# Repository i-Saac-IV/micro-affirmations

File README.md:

# µAffirmations
A microcontroller-based affection-giving MACHINE!

> [!IMPORTANT]
> This project is currently a work-in-progress, there __will__ be things that don't work, please bear with me will I work out the kinks!

# Table of Contents
- [Usage Guide](#usage-guide)
  - [Hardware](#hardware)
  - [Firmware](#firmware)
- [Photos](#photos)
- [Project Updates](#project-updates)
- [Copyright and Licensing](#copyright-and-licensing)
- [Contact](#contact)

# Usage Guide
## Hardware
The PCB files can be found [here](/hw/pcb/micro-affirmations.zip), be sure of order a solder stencil too(ideally with a stencil unless you love hand-soldering 200+ SMD connections). The [BOM](/hw/pcb/bom/ibom.html) will provide you with a list of parts required and their placements. Due to the limited size on the PCB, many of the reference designators have been removed to save space. Because of this, you will likely need to have KiCAD or the iBOM running as you are placing components. Or you can guess I suppose...

## Firmware
You will need access to an ST-Link programming device and have [stm32-for-vscode](https://open-vsx.org/extension/bmd/stm32-for-vscode) extension installed. Once you're ready, upload the code by:
- Cloning the repository
- Open in VS code
- Connect the ST-Link programmer to your computer
- Connect the µAffirmations' programming port to the ST-Link programmer
- Ensure the µAffirmations board is powered
- Open the STM32 for VS Code extention
- Click __Flash STM32__

### Message customisation
This device allows the user to create their own custom messages to be displayed on the LED matrix, to provide your messages, modify the following code found in [this](/Core/Src/messages.c) file.

For axample:
```c
__weak const char *messages[] = {
    "This is the first custom message!",
    "Below is a list of supported characters...",
    "!\"#$%&'()*+,-./0123456789:;<=>?@ABCDEFGHIJKLMNOPQRSTUVWXYZ[\\]^_`abcdefghijklmnopqrstuvwxyz{|}~"
};
```

# Photos
<table align="center">
  <tr>
    <td align="center">
      <br>
      <b>Programming port broken in RevB of the PCB</b>
    </td>
  </tr>
</table>

# Project Updates
## Hardware [RevD](https://github.com/i-Saac-IV/micro-affirmations/tree/v0.9.3)
After considerable development to the code, I found out that I had not connected the supercapacitor voltage sensing circuit to a ADC capable pin, this has been corrected. I also found that if the input voltage of the charging IC is greater than the output voltage = 100mV the bucking function of the IC is bypassed (meaning if the input is 5V the output is also 5V, bad for the STM chip), this has been fixed with the linear regulator.

## Hardware [RevC](https://github.com/i-Saac-IV/micro-affirmations/tree/v0.9.2)
After futher testing the following fixes to the hardware design have been made:
- The programming port has been connected to the correct pins on the mircocontroller
- The layout of the components has been adjusted for easier access to the push button
- The supercapacitor management circuit has been de-routed as per the spec sheet
- I added a QR to the PCB, because I could...

## Hardware [RevB](https://github.com/i-Saac-IV/micro-affirmations/tree/v0.9.1)
After hardware tesing the following fixes have been made to the hardware design:
- Supercapacitor charging circuit, now uses a dedecated IC
- LED matrix layout, the LED spacing has been decreased
- LED brightness was assessed and appropriate resistor have been selected
- The overall PCB dimentions have shrunk to 70x40mm
<table align="center">
  <tr>
    <td align="center">
      <br>
      <b>RevB PCB</b>
    </td>
  </tr>
</table>

## Hardware [RevA](https://github.com/i-Saac-IV/micro-affirmations/tree/v0.9.0)
Initial hardware design.

# Copyright and Licensing
See [licence](LICENSE) for in depth info.
<!--
This project uses the following third-party libraries:

- Lib ( License)

Copyright and license terms belong to their respective authors.

Contact me if anything here is incorrect.
-->

# Contact
If you'd like to get in touch, feel free to reach out!
<p>

</p>

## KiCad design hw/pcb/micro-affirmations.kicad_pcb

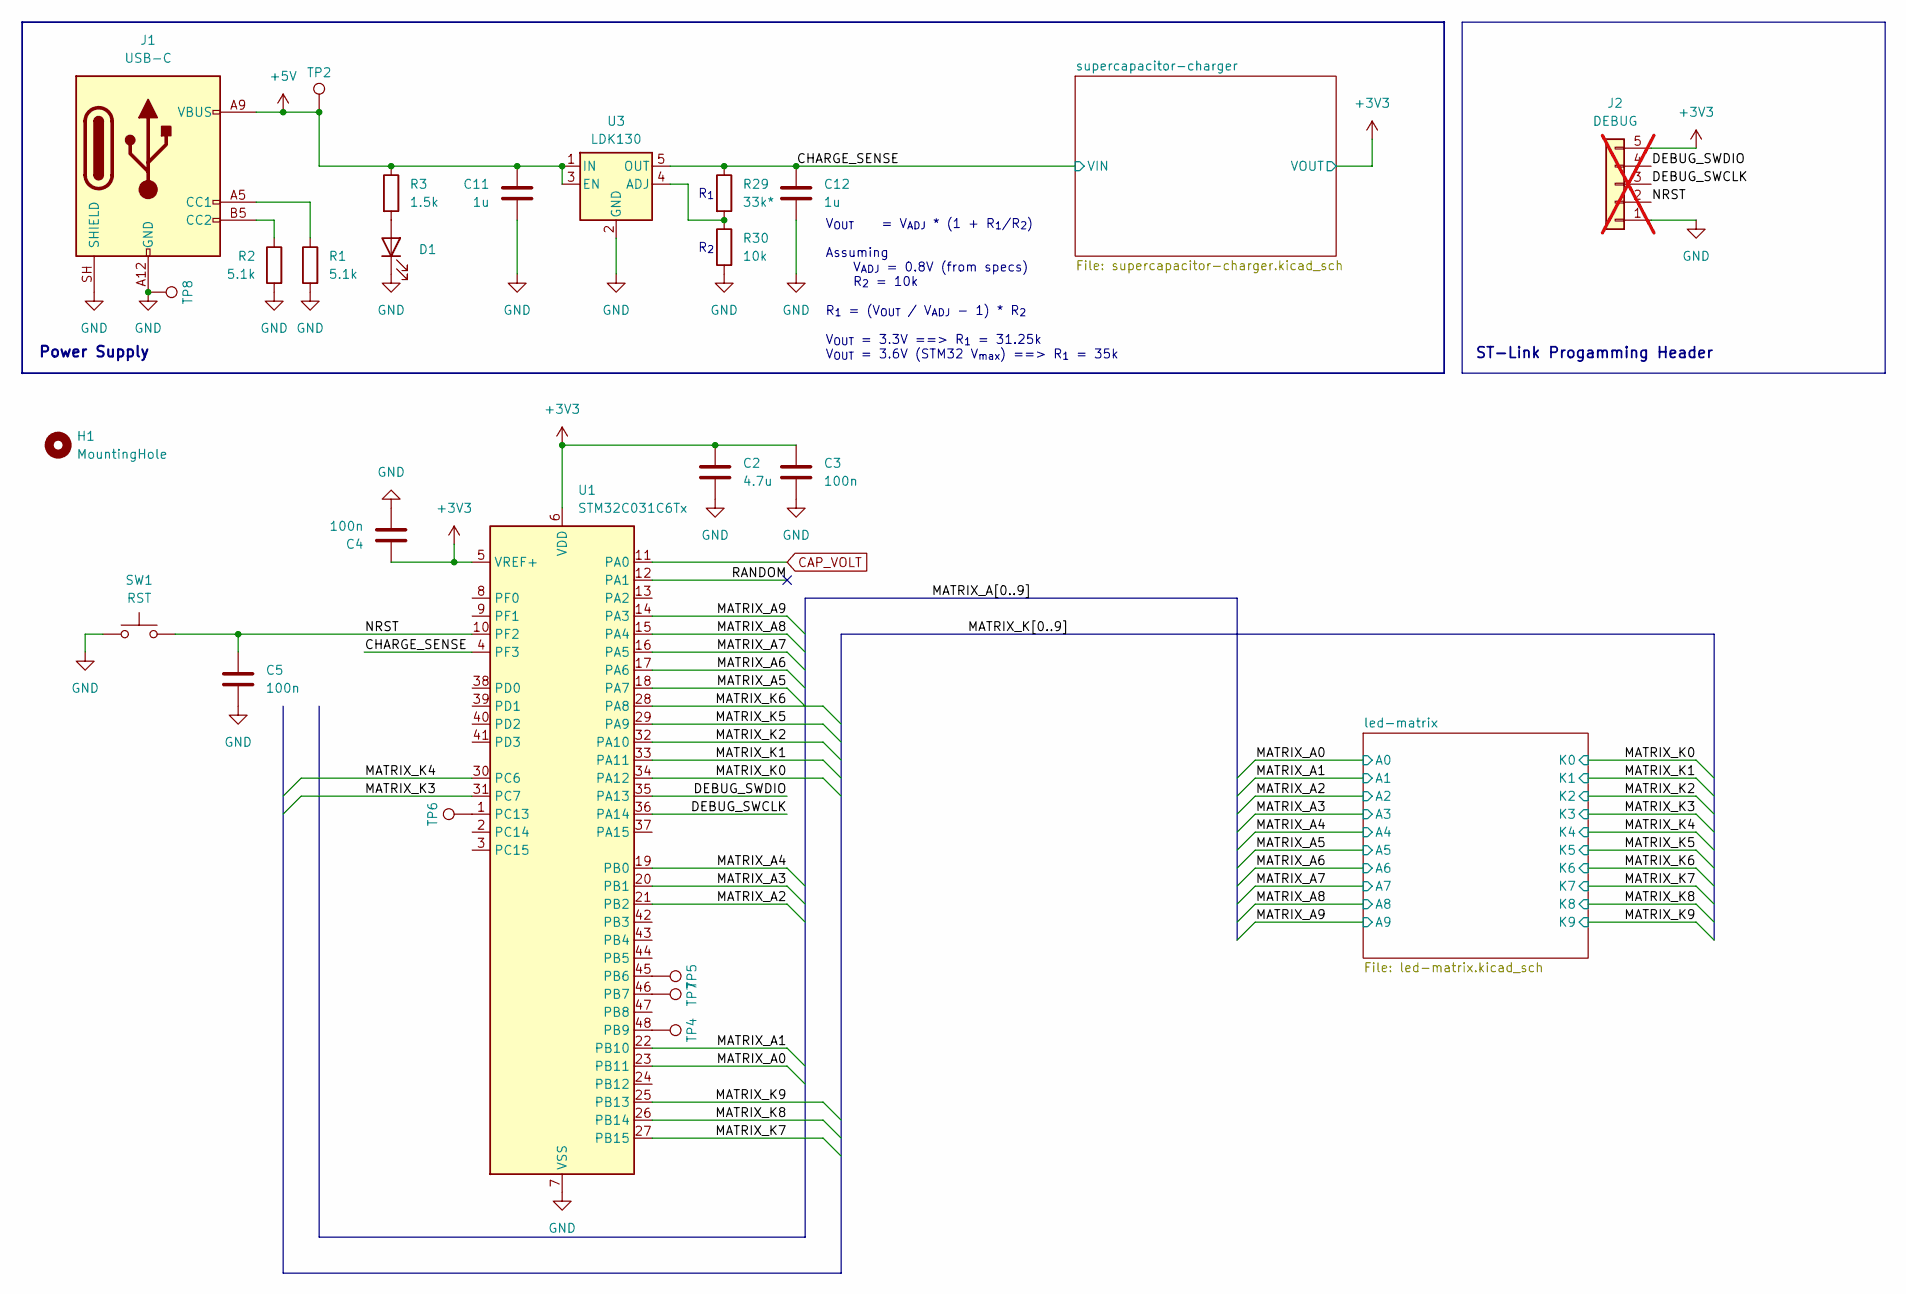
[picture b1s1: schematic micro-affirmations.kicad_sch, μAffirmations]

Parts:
C2: 4.7u; C_0805_2012Metric
C3, C4, C5: 100n; C_0805_2012Metric
C11, C12: 1u; C_0603_1608Metric
D1: CHARGE; D_0603_1608Metric
H1: MountingHole; MountingHole_2.2mm_M2
J1: USB-C; 2171750001_MOL
J2: DEBUG; PinHeader_1x05_P2.54mm_Vertical; not fitted
R1, R2: 5.1k; R_0603_1608Metric
R3: 1.5k; R_0603_1608Metric
R29: 33k*; R_0603_1608Metric
R30: 10k; R_0603_1608Metric
SW1: RST; TL1030_A
TP2, TP4, TP5, TP6, TP7, TP8: TestPoint; TestPoint_Pad_D1.0mm
U1: STM32C031C6Tx; LQFP-48_7x7mm_P0.5mm
U3: LDK130; SOT-23-5

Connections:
+3V3: C2.1, C3.1, C4.1, J2.5, U1.5 (VREF+), U1.6 (VDD); also elsewhere on the board
+5V: C11.1, J1.A9 (VBUS), J1.B9 (VBUS), R3.1, TP2.1 (1_1), U3.1 (IN), U3.3 (EN)
/CHARGE_SENSE: C12.1, R29.1, U1.4 (PF3), U3.5 (OUT); also elsewhere on the board
/DEBUG_SWCLK: J2.3, U1.36 (PA14)
/DEBUG_SWDIO: J2.4, U1.35 (PA13)
/MATRIX_A0: U1.23 (PB11); also elsewhere on the board
/MATRIX_A1: U1.22 (PB10); also elsewhere on the board
/MATRIX_A2: U1.21 (PB2); also elsewhere on the board
/MATRIX_A3: U1.20 (PB1); also elsewhere on the board
/MATRIX_A4: U1.19 (PB0); also elsewhere on the board
/MATRIX_A5: U1.18 (PA7); also elsewhere on the board
/MATRIX_A6: U1.17 (PA6); also elsewhere on the board
/MATRIX_A7: U1.16 (PA5); also elsewhere on the board
/MATRIX_A8: U1.15 (PA4); also elsewhere on the board
/MATRIX_A9: U1.14 (PA3); also elsewhere on the board
/MATRIX_K0: U1.34 (PA12); also elsewhere on the board
/MATRIX_K1: U1.33 (PA11); also elsewhere on the board
/MATRIX_K2: U1.32 (PA10); also elsewhere on the board
/MATRIX_K3: U1.31 (PC7); also elsewhere on the board
/MATRIX_K4: U1.30 (PC6); also elsewhere on the board
/MATRIX_K5: U1.29 (PA9); also elsewhere on the board
/MATRIX_K6: U1.28 (PA8); also elsewhere on the board
/MATRIX_K7: U1.27 (PB15); also elsewhere on the board
/MATRIX_K8: U1.26 (PB14); also elsewhere on the board
/MATRIX_K9: U1.25 (PB13); also elsewhere on the board
/NRST: C5.1, J2.2, SW1.2, U1.10 (PF2)
/RANDOM: U1.12 (PA1)
CAP_VOLT: U1.11 (PA0); also elsewhere on the board
GND: C2.2, C3.2, C4.2, C5.2, C11.2, C12.2, D1.1 (K), J1.A12 (GND), J1.B12 (GND), J1.SH (SHIELD), J2.1, R1.2, R2.2, R30.2, SW1.1, TP8.1 (1_1), U1.7 (VSS), U3.2 (GND); also elsewhere on the board
unnamed: D1.2 (A), R3.2
unnamed: J1.A5 (CC1), R1.1
unnamed: J1.B5 (CC2), R2.1
unnamed: TP5.1 (1_1), U1.45 (PB6)
unnamed: TP7.1 (1_1), U1.46 (PB7)
unnamed: TP4.1 (1_1), U1.48 (PB9)
unnamed: TP6.1 (1_1), U1.1 (PC13)
unnamed: R29.2, R30.1, U3.4 (ADJ)

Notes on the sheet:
ST-Link Progamming Header
R_{1}
R_{2}
Power Supply
V_{OUT} = V_{ADJ} * (1 + R_{1}/R_{2}) Assuming V_{ADJ} = 0.8V (from specs) R_{2} = 10k R_{1} = (V_{OUT} / V_{ADJ} - 1) * R_{2} V_{OUT} = 3.3V ==> R_{1} = 31.25k V_{OUT} = 3.6V (STM32 V_{max}) ==> R_{1} = 35k

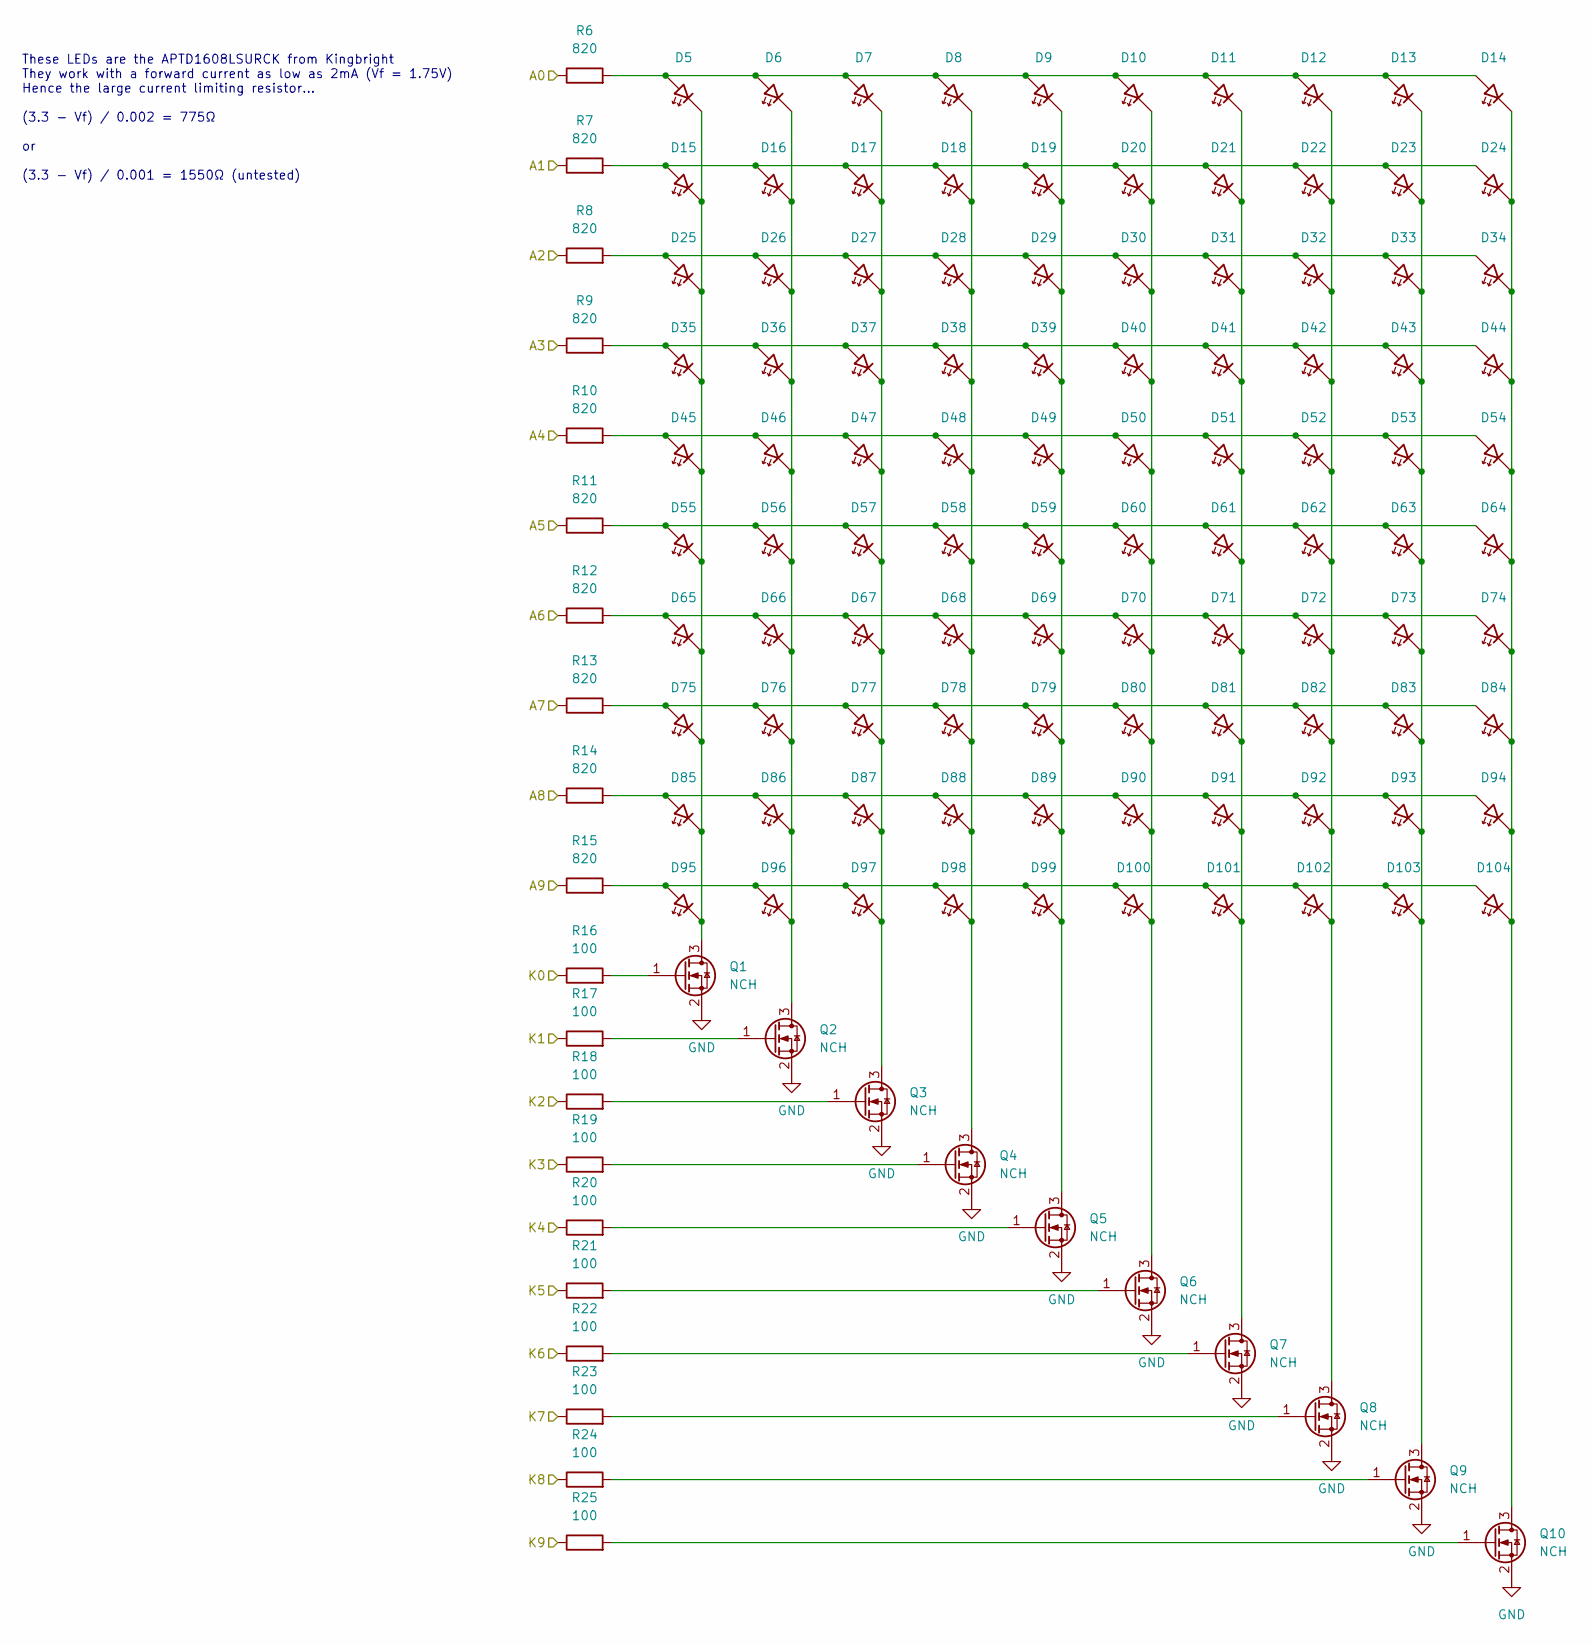
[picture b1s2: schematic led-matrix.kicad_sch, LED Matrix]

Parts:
D5, D6, D7, D8, D9, D10, D11, D12, D13, D14, D15, D16, D17, D18, D19, D20, D21, D22, D23, D24, D25, D26, D27, D28, D29, D30, D31, D32, D33, D34, D35, D36, D37, D38, D39, D40, D41, D42, D43, D44, D45, D46, D47, D48, D49, D50, D51, D52, D53, D54, D55, D56, D57, D58, D59, D60, D61, D62, D63, D64, D65, D66, D67, D68, D69, D70, D71, D72, D73, D74, D75, D76, D77, D78, D79, D80, D81, D82, D83, D84, D85, D86, D87, D88, D89, D90, D91, D92, D93, D94, D95, D96, D97, D98, D99, D100, D101, D102, D103, D104: LED; D_0603_1608Metric
Q1, Q2, Q3, Q4, Q5, Q6, Q7, Q8, Q9, Q10: NCH; SOT-416
R6, R7, R8, R9, R10, R11, R12, R13, R14, R15: 820; R_0603_1608Metric
R16, R17, R18, R19, R20, R21, R22, R23, R24, R25: 100; R_0603_1608Metric

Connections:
/MATRIX_A0: R6.1; also elsewhere on the board
/MATRIX_A1: R7.1; also elsewhere on the board
/MATRIX_A2: R8.1; also elsewhere on the board
/MATRIX_A3: R9.1; also elsewhere on the board
/MATRIX_A4: R10.1; also elsewhere on the board
/MATRIX_A5: R11.1; also elsewhere on the board
/MATRIX_A6: R12.1; also elsewhere on the board
/MATRIX_A7: R13.1; also elsewhere on the board
/MATRIX_A8: R14.1; also elsewhere on the board
/MATRIX_A9: R15.1; also elsewhere on the board
/MATRIX_K0: R16.1; also elsewhere on the board
/MATRIX_K1: R17.1; also elsewhere on the board
/MATRIX_K2: R18.1; also elsewhere on the board
/MATRIX_K3: R19.1; also elsewhere on the board
/MATRIX_K4: R20.1; also elsewhere on the board
/MATRIX_K5: R21.1; also elsewhere on the board
/MATRIX_K6: R22.1; also elsewhere on the board
/MATRIX_K7: R23.1; also elsewhere on the board
/MATRIX_K8: R24.1; also elsewhere on the board
/MATRIX_K9: R25.1; also elsewhere on the board
GND: Q1.2 (S), Q2.2 (S), Q3.2 (S), Q4.2 (S), Q5.2 (S), Q6.2 (S), Q7.2 (S), Q8.2 (S), Q9.2 (S), Q10.2 (S); also elsewhere on the board
unnamed: D5.2 (A), D6.2 (A), D7.2 (A), D8.2 (A), D9.2 (A), D10.2 (A), D11.2 (A), D12.2 (A), D13.2 (A), D14.2 (A), R6.2
unnamed: D10.1 (K), D20.1 (K), D30.1 (K), D40.1 (K), D50.1 (K), D60.1 (K), D70.1 (K), D80.1 (K), D90.1 (K), D100.1 (K), Q6.3 (D)
unnamed: D15.2 (A), D16.2 (A), D17.2 (A), D18.2 (A), D19.2 (A), D20.2 (A), D21.2 (A), D22.2 (A), D23.2 (A), D24.2 (A), R7.2
unnamed: D5.1 (K), D15.1 (K), D25.1 (K), D35.1 (K), D45.1 (K), D55.1 (K), D65.1 (K), D75.1 (K), D85.1 (K), D95.1 (K), Q1.3 (D)
unnamed: D6.1 (K), D16.1 (K), D26.1 (K), D36.1 (K), D46.1 (K), D56.1 (K), D66.1 (K), D76.1 (K), D86.1 (K), D96.1 (K), Q2.3 (D)
unnamed: D7.1 (K), D17.1 (K), D27.1 (K), D37.1 (K), D47.1 (K), D57.1 (K), D67.1 (K), D77.1 (K), D87.1 (K), D97.1 (K), Q3.3 (D)
unnamed: D8.1 (K), D18.1 (K), D28.1 (K), D38.1 (K), D48.1 (K), D58.1 (K), D68.1 (K), D78.1 (K), D88.1 (K), D98.1 (K), Q4.3 (D)
unnamed: D9.1 (K), D19.1 (K), D29.1 (K), D39.1 (K), D49.1 (K), D59.1 (K), D69.1 (K), D79.1 (K), D89.1 (K), D99.1 (K), Q5.3 (D)
unnamed: D25.2 (A), D26.2 (A), D27.2 (A), D28.2 (A), D29.2 (A), D30.2 (A), D31.2 (A), D32.2 (A), D33.2 (A), D34.2 (A), R8.2
unnamed: D35.2 (A), D36.2 (A), D37.2 (A), D38.2 (A), D39.2 (A), D40.2 (A), D41.2 (A), D42.2 (A), D43.2 (A), D44.2 (A), R9.2
unnamed: D45.2 (A), D46.2 (A), D47.2 (A), D48.2 (A), D49.2 (A), D50.2 (A), D51.2 (A), D52.2 (A), D53.2 (A), D54.2 (A), R10.2
unnamed: D55.2 (A), D56.2 (A), D57.2 (A), D58.2 (A), D59.2 (A), D60.2 (A), D61.2 (A), D62.2 (A), D63.2 (A), D64.2 (A), R11.2
unnamed: D65.2 (A), D66.2 (A), D67.2 (A), D68.2 (A), D69.2 (A), D70.2 (A), D71.2 (A), D72.2 (A), D73.2 (A), D74.2 (A), R12.2
unnamed: D75.2 (A), D76.2 (A), D77.2 (A), D78.2 (A), D79.2 (A), D80.2 (A), D81.2 (A), D82.2 (A), D83.2 (A), D84.2 (A), R13.2
unnamed: D85.2 (A), D86.2 (A), D87.2 (A), D88.2 (A), D89.2 (A), D90.2 (A), D91.2 (A), D92.2 (A), D93.2 (A), D94.2 (A), R14.2
unnamed: D95.2 (A), D96.2 (A), D97.2 (A), D98.2 (A), D99.2 (A), D100.2 (A), D101.2 (A), D102.2 (A), D103.2 (A), D104.2 (A), R15.2
unnamed: D11.1 (K), D21.1 (K), D31.1 (K), D41.1 (K), D51.1 (K), D61.1 (K), D71.1 (K), D81.1 (K), D91.1 (K), D101.1 (K), Q7.3 (D)
unnamed: D12.1 (K), D22.1 (K), D32.1 (K), D42.1 (K), D52.1 (K), D62.1 (K), D72.1 (K), D82.1 (K), D92.1 (K), D102.1 (K), Q8.3 (D)
unnamed: D13.1 (K), D23.1 (K), D33.1 (K), D43.1 (K), D53.1 (K), D63.1 (K), D73.1 (K), D83.1 (K), D93.1 (K), D103.1 (K), Q9.3 (D)
unnamed: D14.1 (K), D24.1 (K), D34.1 (K), D44.1 (K), D54.1 (K), D64.1 (K), D74.1 (K), D84.1 (K), D94.1 (K), D104.1 (K), Q10.3 (D)
unnamed: Q1.1 (G), R16.2
unnamed: Q2.1 (G), R17.2
unnamed: Q3.1 (G), R18.2
unnamed: Q4.1 (G), R19.2
unnamed: Q5.1 (G), R20.2
unnamed: Q6.1 (G), R21.2
unnamed: Q7.1 (G), R22.2
unnamed: Q8.1 (G), R23.2
unnamed: Q9.1 (G), R24.2
unnamed: Q10.1 (G), R25.2

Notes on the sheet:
These LEDs are the APTD1608LSURCK from Kingbright They work with a forward current as low as 2mA (Vf = 1.75V) Hence the large current limiting resistor... (3.3 - Vf) / 0.002 = 775Ω or (3.3 - Vf) / 0.001 = 1550Ω (untested)

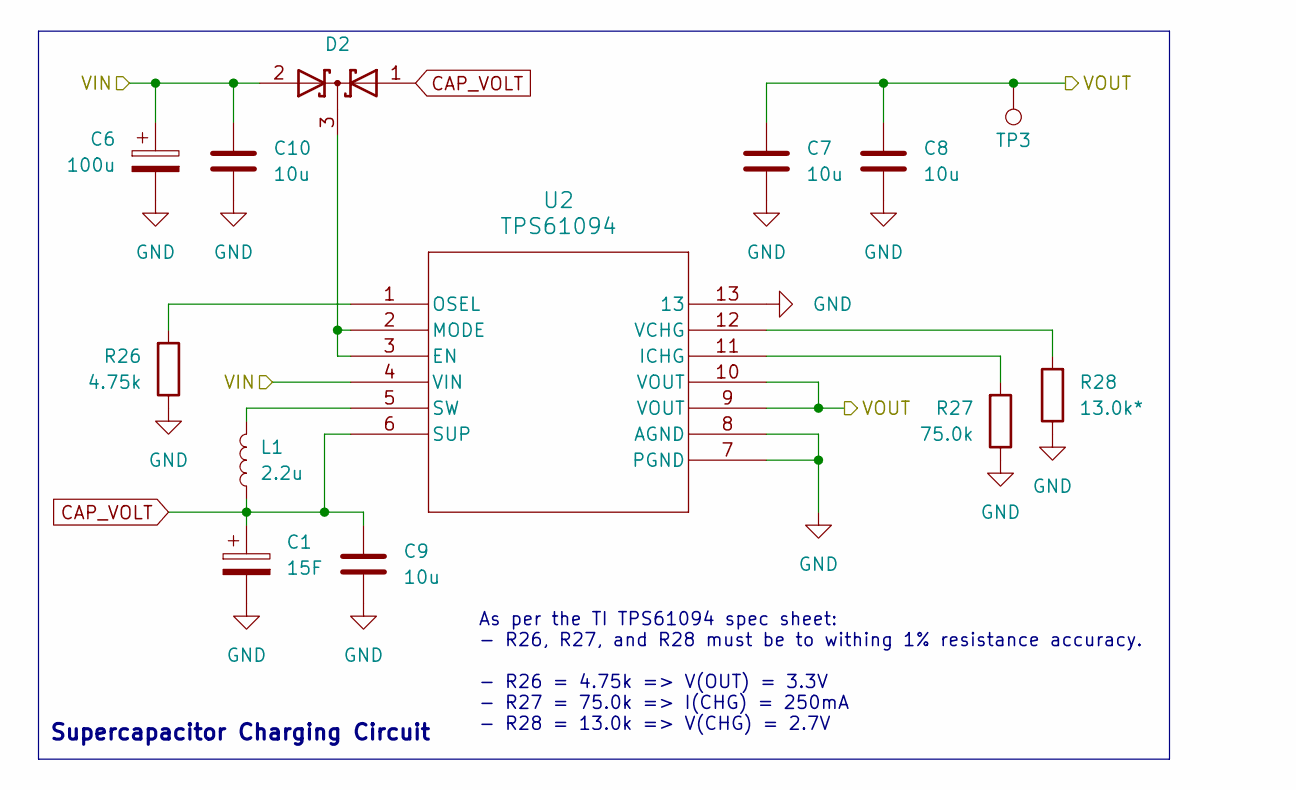
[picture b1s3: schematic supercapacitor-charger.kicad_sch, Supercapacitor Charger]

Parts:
C1: 15F; CP_Radial_L32.0mm_D12.5mm_P5.00mm_Horizontal
C6: 100u; CP_Elec_6.3x5.4_Nichicon
C7, C8, C9, C10: 10u; C_0805_2012Metric
D2: SOT-23
L1: 2.2u; L_1616_4040Metric
R26: 4.75k; R_0603_1608Metric
R27: 75.0k; R_0603_1608Metric
R28: 13.0k*; R_0603_1608Metric
TP3: TestPoint; TestPoint_Pad_D1.0mm
U2: TPS61094; WSON_94DSSR_TEX

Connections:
+3V3: C7.1, C8.1, TP3.1 (1_1), U2.9 (VOUT), U2.10 (VOUT); also elsewhere on the board
/CHARGE_SENSE: C6.1, C10.1, D2.2 (A), U2.4 (VIN); also elsewhere on the board
CAP_VOLT: C1.1, C9.1, D2.1 (A), L1.2, U2.6 (SUP); also elsewhere on the board
GND: C1.2, C6.2, C7.2, C8.2, C9.2, C10.2, R26.1, R27.1, R28.1, U2.7 (PGND), U2.8 (AGND), U2.13; also elsewhere on the board
unnamed: D2.3 (K), U2.2 (MODE), U2.3 (EN)
unnamed: R27.2, U2.11 (ICHG)
unnamed: R26.2, U2.1 (OSEL)
unnamed: L1.1, U2.5 (SW)
unnamed: R28.2, U2.12 (VCHG)

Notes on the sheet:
As per the TI TPS61094 spec sheet: - R26, R27, and R28 must be to withing 1% resistance accuracy. - R26 = 4.75k => V(OUT) = 3.3V - R27 = 75.0k => I(CHG) = 250mA - R28 = 13.0k => V(CHG) = 2.7V
Supercapacitor Charging Circuit

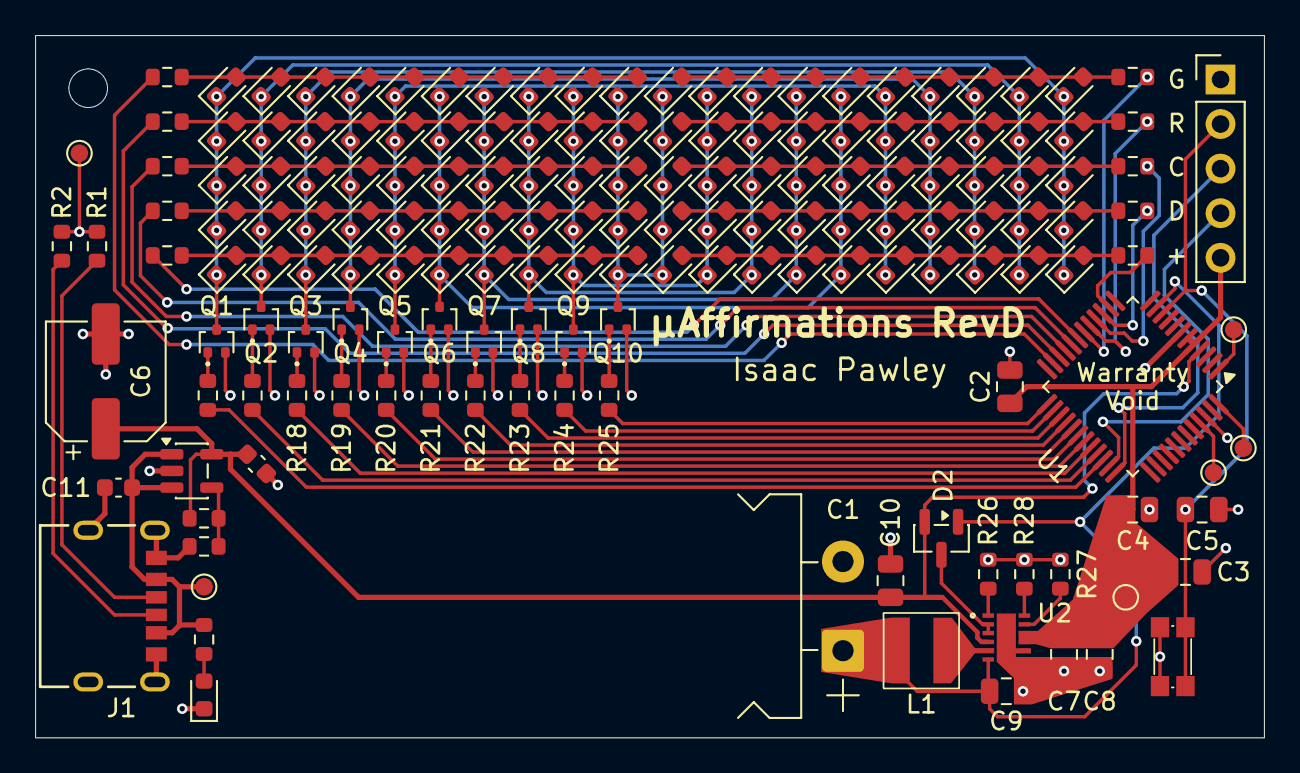
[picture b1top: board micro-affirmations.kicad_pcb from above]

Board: 2 copper layers, 70.0 x 40.0 mm, 167 parts (1 on the bottom side), 71 nets.

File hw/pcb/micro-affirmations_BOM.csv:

"Reference","Value","Qty","PN","Footprint"
"U3","LDK130","1","LDK130M-R","Package_TO_SOT_SMD:SOT-23-5"
"U2","TPS61094","1","TPS61094DSSR","micro-affirmations_footprints:WSON_94DSSR_TEX"
"U1","STM32C031C6Tx","1","STM32C031C6T6TR","Package_QFP:LQFP-48_7x7mm_P0.5mm"
"SW1","RST","1","TL1030AF350AQJ","micro-affirmations_footprints:TL1030_A"
"R30","10k","1","CRGCQ0603F10K","Resistor_SMD:R_0603_1608Metric"
"R29","33k","1","CRGCQ0603F33K ","Resistor_SMD:R_0603_1608Metric"
"R28","13.0k","1","CPF0603F13KC1","Resistor_SMD:R_0603_1608Metric"
"R27","75.0k","1","CPF0603F75KC1","Resistor_SMD:R_0603_1608Metric"
"R26","4.75k","1","CPF0603F4K75C1","Resistor_SMD:R_0603_1608Metric"
"R16,R17,R18,R19,R20,R21,R22,R23,R24,R25","100","10","CRGCQ0603F100R","Resistor_SMD:R_0603_1608Metric"
"R6,R7,R8,R9,R10,R11,R12,R13,R14,R15","820","10","CRGCQ0603F820R","Resistor_SMD:R_0603_1608Metric"
"R3","1.5k","1","CRGCQ0603F1K5","Resistor_SMD:R_0603_1608Metric"
"R1,R2","5.1k","2","CRG0603F5K1","Resistor_SMD:R_0603_1608Metric"
"Q1,Q2,Q3,Q4,Q5,Q6,Q7,Q8,Q9,Q10","NCH","10","SSM3K37FS,LF","Package_TO_SOT_SMD:SOT-416"
"L1","2.2u","1","74438356022","micro-affirmations_footprints:L_1616_4040Metric"
"J1","USB-C","1","217175-0001","micro-affirmations_footprints:2171750001_MOL"
"D5,D6,D7,D8,D9,D10,D11,D12,D13,D14,D15,D16,D17,D18,D19,D20,D21,D22,D23,D24,D25,D26,D27,D28,D29,D30,D31,D32,D33,D34,D35,D36,D37,D38,D39,D40,D41,D42,D43,D44,D45,D46,D47,D48,D49,D50,D51,D52,D53,D54,D55,D56,D57,D58,D59,D60,D61,D62,D63,D64,D65,D66,D67,D68,D69,D70,D71,D72,D73,D74,D75,D76,D77,D78,D79,D80,D81,D82,D83,D84,D85,D86,D87,D88,D89,D90,D91,D92,D93,D94,D95,D96,D97,D98,D99,D100,D101,D102,D103,D104","LED","100","APTD1608LSURCK","Diode_SMD:D_0603_1608Metric"
"D1","CHARGE","1","APTD1608LCGCK","Diode_SMD:D_0603_1608Metric"
"C11,C12","1u","2","C0603C105K3RACTU ","Capacitor_SMD:C_0603_1608Metric"
"C7,C8,C9,C10","10u","4","C0805C106K8PACTU","Capacitor_SMD:C_0805_2012Metric"
"C6","100u","1","UWT1A101MCL1GB","Capacitor_SMD:CP_Elec_6.3x5.4_Nichicon"
"C3,C4,C5","100n","3","C0805F104K1RACAUTO","Capacitor_SMD:C_0805_2012Metric"
"C2","4.7u","1","C0805C475K4RACTU","Capacitor_SMD:C_0805_2012Metric"
"C1","15F","1","MAL223051016E3","micro-affirmations_footprints:CP_Radial_L32.0mm_D12.5mm_P5.00mm_Horizontal"

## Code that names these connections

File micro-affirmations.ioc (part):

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Mcu.Name=STM32C031C(4-6)Tx
Mcu.Package=LQFP48
Mcu.UserName=STM32C031C6Tx
PA0.GPIOParameters=GPIO_Label
PA0.GPIO_Label=CAP_VOLT
PA0.Mode=IN0
PA0.Signal=ADC1_IN0
PA1.GPIOParameters=GPIO_Label
PA1.GPIO_Label=RANDOM
PA1.Mode=IN1
PA1.Signal=ADC1_IN1
PA10.GPIOParameters=GPIO_Label
PA10.GPIO_Label=MATRIX_K2
PA10.Signal=GPIO_Output
PA11\ [PA9].GPIOParameters=GPIO_Label
PA11\ [PA9].GPIO_Label=MATRIX_K1
PA11\ [PA9].Signal=GPIO_Output
PA12\ [PA10].GPIOParameters=GPIO_Label
PA12\ [PA10].GPIO_Label=MATRIX_K0
PA12\ [PA10].Signal=GPIO_Output
PA13.Mode=Serial_Wire
PA13.Signal=DEBUG_SWDIO
PA14-BOOT0.Mode=Serial_Wire
PA14-BOOT0.Signal=DEBUG_SWCLK
PA3.GPIOParameters=GPIO_Label
PA3.GPIO_Label=MATRIX_A9
PA3.Signal=GPIO_Output
PA4.GPIOParameters=GPIO_Label
PA4.GPIO_Label=MATRIX_A8
PA4.Signal=GPIO_Output
PA5.GPIOParameters=GPIO_Label
PA5.GPIO_Label=MATRIX_A7
PA5.Signal=GPIO_Output
PA6.GPIOParameters=GPIO_Label
PA6.GPIO_Label=MATRIX_A6
PA6.Signal=GPIO_Output
PA7.GPIOParameters=GPIO_Label
PA7.GPIO_Label=MATRIX_A5
PA7.Signal=GPIO_Output
PA8.GPIOParameters=GPIO_Label
PA8.GPIO_Label=MATRIX_K6
PA8.Signal=GPIO_Output
PA9.GPIOParameters=GPIO_Label
PA9.GPIO_Label=MATRIX_K5
PA9.Signal=GPIO_Output
PB0.GPIOParameters=GPIO_Label
PB0.GPIO_Label=MATRIX_A4
PB0.Signal=GPIO_Output
PB1.GPIOParameters=GPIO_Label
PB1.GPIO_Label=MATRIX_A3
PB1.Signal=GPIO_Output
PB10.GPIOParameters=GPIO_Label
PB10.GPIO_Label=MATRIX_A1
PB10.Signal=GPIO_Output
PB11.GPIOParameters=GPIO_Label
PB11.GPIO_Label=MATRIX_A0
PB11.Signal=GPIO_Output
PB13.GPIOParameters=GPIO_Label
PB13.GPIO_Label=MATRIX_K9
PB13.Signal=GPIO_Output
PB14.GPIOParameters=GPIO_Label
PB14.GPIO_Label=MATRIX_K8
PB14.Signal=GPIO_Output
PB15.GPIOParameters=GPIO_Label
PB15.GPIO_Label=MATRIX_K7
PB15.Signal=GPIO_Output
PB2.GPIOParameters=GPIO_Label
PB2.GPIO_Label=MATRIX_A2
PB2.Signal=GPIO_Output
PC6.GPIOParameters=GPIO_Label
PC6.GPIO_Label=MATRIX_K4
PC6.Signal=GPIO_Output
PC7.GPIOParameters=GPIO_Label
PC7.GPIO_Label=MATRIX_K3
PC7.Signal=GPIO_Output
PF3.GPIOParameters=GPIO_Label
PF3.GPIO_Label=CHARGE_SENSE
PF3.Signal=GPIO_Input
RCC.HSE_VALUE=8000000
RCC.SYSCLKFreq_VALUE=48000000
board=custom

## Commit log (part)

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2026-04-08 chore: updated gitignore for kicad, mxcube and vscode
2026-04-08 docs: updated readme to have project title and basic description
2026-04-08 chore: added initial kicad files
2026-04-08 chore: added initial stm32 files
2026-04-11 feat: added usb-c footprint
2026-04-11 feat: added supercapacitor footprint
2026-04-11 feat: added button footprint
2026-04-11 chore: added symbol and footprint libraries
2026-04-11 feat: completed initail hardware design
2026-04-11 chore: completed initail software configuration
2026-04-13 fix: added programming and debug port to schematic
2026-04-13 chore: component footprint layout complete
2026-04-14 fix: updated programming and debug port to include nrst
2026-04-14 feat: completed pcb layout for revision a
2026-04-14 feat: added gerbers of revision a
2026-04-14 chore: updated gitignore to exclude raw gerber files
2026-05-11 chore: added inductor footprint
2026-05-11 chore: added charger ic symbol
2026-05-11 feat: added improved circuit for charging supercapacitor
2026-05-11 feat: revision b pcb generated
2026-05-11 docs: added revision b bom
2026-05-11 fix: changed bom name
2026-05-30 fix: removed email from readme
